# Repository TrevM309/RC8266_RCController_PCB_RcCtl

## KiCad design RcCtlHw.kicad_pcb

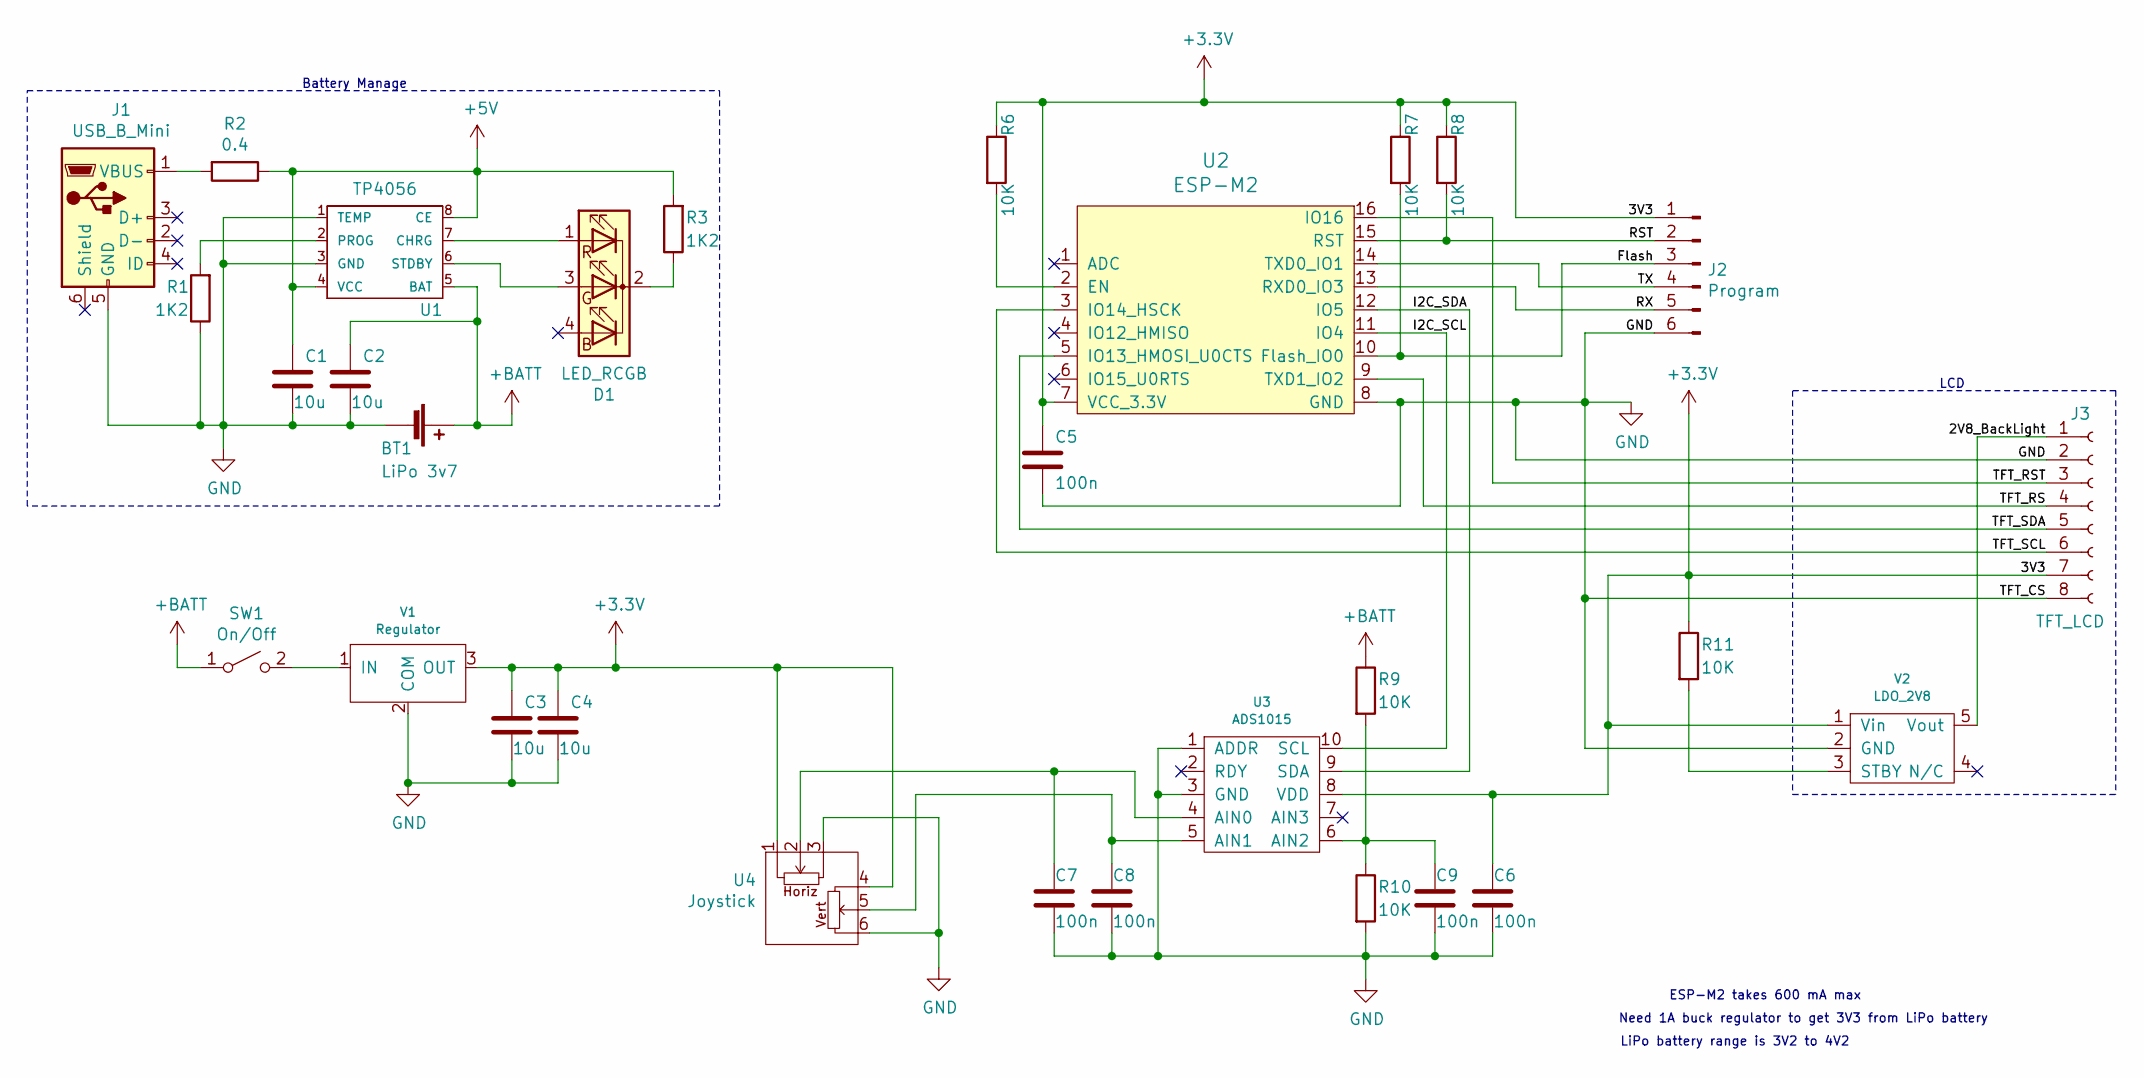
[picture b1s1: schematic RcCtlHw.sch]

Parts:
BT1: LiPo 3v7; PinHeader_1x02_P2.54mm_Vertical
C1, C2, C3, C4: 10u; C_0805_2012Metric
C5, C6, C7, C8, C9: 100n; C_0805_2012Metric
D1: LED_RCGB; LED_D5.0mm-4_RGB-RIGHT
J1: USB_B_Mini; USB_micro
J2: Program; PinHeader_1x06_P2.54mm_Vertical_bent
J3: TFT_LCD; 8w_FFC_conn
R1, R3: 1K2; R_0805_2012Metric
R2: 0.4; R_2512_6332Metric
R6, R7, R8, R9, R10, R11: 10K; R_0805_2012Metric
SW1: On/Off; SlideSwitch
U1: TP4056; SOP-8_3.9x4.9mm_P1.27mm
U2: ESP-M2; ESP-M2_DOIT
U3: ADS1015; MSOP-10_3x3mm_P0.5mm
U4: Joystick
V1: Regulator; TO-252-2
V2: LDO_2V8; SOT-353_SC-70-5

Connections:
+3V3: C3.1, C4.1, C5.1, C6.1, J2.1, J3.7, R6.1, R7.1, R8.1, R11.1, U2.7 (VCC_3.3V), U3.8 (VDD), U4.1, U4.4, V1.3 (OUT), V2.1 (Vin)
+BATT: BT1.1 (+), C2.1, R9.1, SW1.1 (A), U1.5 (BAT)
/2V8_BackLight: J3.1, V2.5 (Vout)
/Flash: J2.3, R7.2, U2.10 (Flash_IO0)
/I2C_SCL: U2.11 (IO4), U3.10 (SCL)
/I2C_SDA: U2.12 (IO5), U3.9 (SDA)
/RST: J2.2, R8.2, U2.15 (RST)
/RX: J2.5, U2.13 (RXD0_IO3)
/TFT_RS: J3.4, U2.9 (TXD1_IO2)
/TFT_RST: J3.3, U2.16 (IO16)
/TFT_SCL: J3.6, U2.3 (IO14_HSCK)
/TFT_SDA: J3.5, U2.5 (IO13_HMOSI_U0CTS)
/TX: J2.4, U2.14 (TXD0_IO1)
GND: BT1.2 (-), C1.2, C2.2, C3.2, C4.2, C5.2, C6.2, C7.2, C8.2, C9.2, J1.5 (GND), J2.6, J3.2, J3.8, R1.1, R10.2, U1.1 (TEMP), U1.3 (GND), U2.8 (GND), U3.1 (ADDR), U3.3 (GND), U4.3, U4.6, V1.2 (COM), V2.2 (GND)
unnamed: C1.1, R2.1, R3.2, U1.4 (VCC), U1.8 (CE)
unnamed: C7.1, U3.4 (AIN0), U4.2
unnamed: C8.1, U3.5 (AIN1), U4.5
unnamed: C9.1, R9.2, R10.1, U3.6 (AIN2)
unnamed: D1.1 (RA), U1.7 (CHRG)
unnamed: D1.2 (K), R3.1
unnamed: D1.3 (GA), U1.6 (STDBY)
unnamed: J1.1 (VBUS), R2.2
unnamed: R1.2, U1.2 (PROG)
unnamed: R6.2, U2.2 (EN)
unnamed: R11.2, V2.3 (STBY)
unnamed: SW1.2 (B), V1.1 (IN)

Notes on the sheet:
Battery Manage
LCD
LiPo battery range is 3V2 to 4V2
Need 1A buck regulator to get 3V3 from LiPo battery
ESP-M2 takes 600 mA max

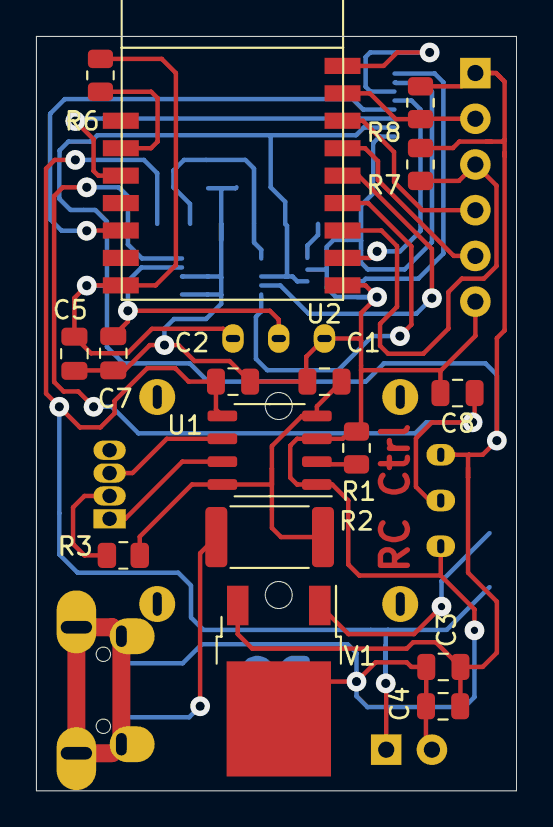
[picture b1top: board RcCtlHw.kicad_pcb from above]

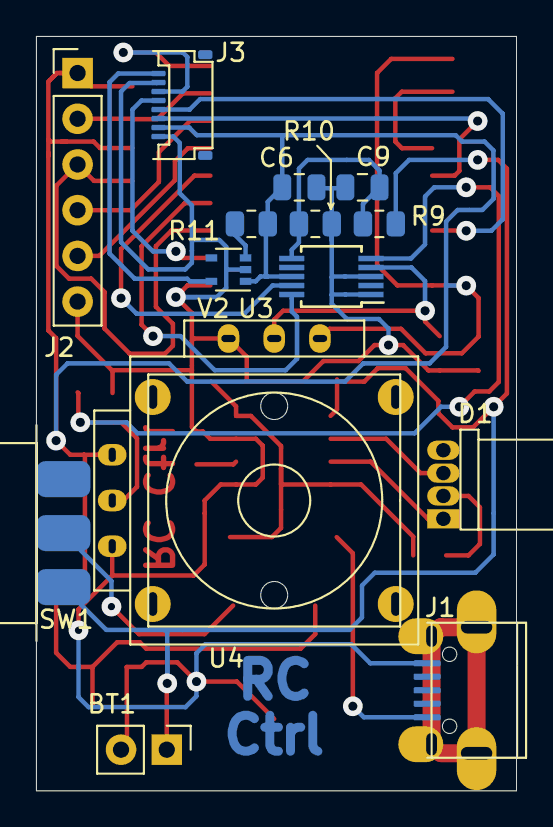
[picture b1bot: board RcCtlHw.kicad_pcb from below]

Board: 2 copper layers, 26.7 x 41.9 mm, 30 parts (14 on the bottom side), 26 nets.

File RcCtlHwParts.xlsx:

Ref | Description | Name | Package | Num | Got | Source | Order | Cost £ | Price |  | got | onorder
U1 | Charging IC | TP4056 | SOP-8 | 1 | y | AliExpress | 20 | 0.76 | 3.7999999999999999E-2 |  | 18
U2 | Main IC | ESP-M2 | ESP-M2 | 1 | y | AliExpress | 1 | 1.1100000000000001 | 1.1100000000000001 |  | 6
U3 | I2C to 4 x ADC | ADS1015 | MSOP10 | 1 | y | AliExpress | 5 | 4.3499999999999996 | 0.86999999999999988 |  | 3 | 20 | aliexpress
V1 | 3V3 regulator | BA033CC0FP-E2 | TO252-3 | 1 | y | Farnell | 1 | 0.87 | 0.87 |  | 1 | 10 | farnell
V2 | 2V8 regulator | MIC5365-2.8YC5-TR | SC-70-5 | 1 | y | Farnell | 5 | 0.56000000000000005 | 0.11200000000000002 |  | 2 | 10 | farnell
D1 | RGB common cathode LED |  | 5mm | 1 | y | AliExpress | 100 | 7.19 | 7.1900000000000006E-2 |  | 98
R1,3 | 1K2 Resistor | MCWR08X1201FTL | 0805 | 2 | y | Farnell | 1 | 8.0000000000000002E-3 | 1.6E-2 |  | 15
R2 | 0R4 1/2w Resistor | WW25PR400FTL | 2512 | 1 | y | Farnell | 10 | 3.75 | 0.375 |  | 6
R6,7,8 | 10K Resistor | 2074334 | 0805 | 5 | y | Farnell | 10 | 0.19500000000000001 | 9.7500000000000003E-2 |  | 23
C1,2,3,4 | 10uF 10V Capacitor | C2012X6S1A106K085AC | 0805 | 4 | y | Farnell | 10 | 0.54 | 0.21600000000000003 |  | 2 | 10 | farnell
C5,6 | 100nF Capacitor | MC0805B104M500CT | 0805 | 2 | y | Farnell | 10 | 0.52 | 0.10400000000000001 |  | 13
BT1 | 3V7 LiPo Battery | 652338 6.5*23*38mm |  | 1 | y | AliExpress | 2 | 4.6399999999999997 | 2.3199999999999998 |  | 3
SW1 | Small slide switch |  |  | 1 | y | BangGood | 10 | 2.44 | 0.24399999999999999 |  | lots
RV1,2 | Joystick |  |  | 1 | y | BangGood | 1 | 2.2599999999999998 | 2.2599999999999998 |  | 2 | 6 | aliexpress
J1 | Mini USB connector |  |  | 1 | y | Ebay | 10 | 1.31 | 0.13100000000000001 |  | 7
J2 | Program port | 5 pin header |  | 0.125 | y | BangGood | 10 | 1.63 | 2.0374999999999997E-2 |  | lots
J3 | LCD flexi connector | TE 2328702-8-FFC/FPC |  | 1 | y | Farnell | 5 | 0.86 | 0.17199999999999999 |  | 2 | 10 | farnell
J3 | 0.96" 80x160 IPS TFT |  |  | 1 | y | AliExpress | 2 | 2.66 | 1.33 |  | sipeed langan nano | 5 | aliexpress
 |  |  |  |  |  |  |  |  | 10.357775

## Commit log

2021-05-12 1st attempt (not good)
2021-05-14 2nd attempt, looking good
2021-05-14 Small tweaks after creating good pcb
2021-05-22 Re-Design with big changes for TFT connection
2021-05-24 TFT_CS now connected GND, GPIO5 back to I2C_SDA PCB linked, mostly working USB connector beefed
2021-05-25 beefed up USB connector mountings, joystick now swings GND to 3V3 on H & V
2021-05-25 update BOM £10.36 each
2021-05-29 Re-worked USB connector and Joystick to allow oval holes for legs Cleaned up tracks
2021-05-30 update BOM spreadsheet with current stock
2021-06-06 Playing 3D, no real change
2021-06-06 More 3D play
2021-06-19 Added 100n capacitors to ADCs
2021-06-20 Clean up silk screens
2021-06-20 Space things out
2021-06-20 pre etch tweaks
2021-06-21 Files for PCB Manufacture
2021-07-26 Move switch to before regulator
2021-08-10 small silk screnn clarification
2021-09-18 Remove Elecrow specific files (out of date)
2021-09-18 Updated gerber files
2021-09-18 ignore zip files
